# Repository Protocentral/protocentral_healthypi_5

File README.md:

<div align="center">

# HealthyPi 5

### The open-source vital signs monitor you can actually build on.

ECG · Respiration · PPG · SpO₂ · Temperature — streamed live over USB, Bluetooth LE or Wi-Fi
from a single Raspberry Pi HAT-sized board.

</div>

---

## Why HealthyPi 5

HealthyPi 5 pairs **high-precision analog front ends** — 18-bit ECG and 22-bit PPG converters from Maxim
and TI — with a design that is open all the way down.

|  |  |
| --- | --- |
| **Five biosignals, one board** | ECG, respiration, PPG, SpO₂ and temperature simultaneously. |
| **Lossless by design** | The RP2040's two cores split acquisition from everything else — 128 SPS sampling is guaranteed by the architecture, not by tuning. |
| **Connect however you like** | USB-C, BLE or Wi-Fi to OpenView — or log to the onboard microSD with no computer attached. |
| **Genuinely open** | CERN-OHL-P v2 hardware, MIT software, [OSHWA-certified IN000046](https://certification.oshwa.org/in000046.html). Commercial use permitted. |
| **Built to extend** | Qwiic/I²C connectors add GSR, EEG, EMG or any other sensor. |

<div align="center">

<p><sub><b>Live in OpenView</b> — ECG, respiration and PPG over BLE, with recording to disk</sub></p>
</div>

## What you can measure

| Signal | Front end | Notes |
| --- | --- | --- |
| **ECG** | Maxim MAX30001 | 18-bit, 128 SPS, 3-electrode cable included |
| **Respiration** | Maxim MAX30001 | Bio-impedance, from the same electrodes |
| **PPG / SpO₂** | TI AFE4400 | 22-bit, red + IR; Nellcor-compatible probe included |
| **Body temperature** | Maxim MAX30205 | Qwiic/I²C skin probe included |
| **Anything else** | Your sensor | Qwiic connectors — GSR, EEG, EMG, … |

## Hardware at a glance

- **RP2040** dual-core ARM Cortex-M0+ main MCU, 16 MB flash
- **ESP32-C3** RISC-V co-processor for Bluetooth LE and Wi-Fi
- **40-pin Raspberry Pi HAT** connector
- **2× USB Type-C** — one per MCU
- **microSD** slot for onboard recording
- **Li-Ion** battery management with USB charging
- **75.5 × 56 × 17 mm**

> Board revisions **5.2 through 5.7 are electrically identical** — one pin map serves all of them.

## Get started

**1. Get a board** — [ProtoCentral Store](https://protocentral.com/product/healthypi-5-vital-signs-monitoring-hat-kit/) · [Mouser](https://www.mouser.com/c/?m=ProtoCentral&q=HealthyPi%205) · [Crowd Supply](https://www.crowdsupply.com/protocentral/healthypi-5)

**2. Install [OpenView](https://github.com/Protocentral/protocentral_openview/releases)** — Windows, macOS, Linux, Android or iOS.

**3. Connect** over USB, BLE or Wi-Fi and start streaming. Boards ship pre-flashed.

Then see the [documentation](https://protocentral.com/product/healthypi-5-vital-signs-monitoring-hat-kit/docs/) for electrode placement, wiring and the streaming data format.

<div align="center">

<p><sub><b>In the kit</b> — board, SpO₂ probe, ECG cable, temperature probe, headers and 20 electrodes</sub></p>
</div>

## Software & documentation

This repository holds the **hardware design files**. Everything else lives in its own repository:

| | Repository | What it is |
| --- | --- | --- |
| **App** | [protocentral_openview](https://github.com/Protocentral/protocentral_openview) | **OpenView** — the main GUI. Flutter app for Windows, macOS, Linux, Android and iOS. [Downloads](https://github.com/Protocentral/protocentral_openview/releases) |
| **Firmware** (RP2040) | [protocentral_healthypi_5_firmware](https://github.com/Protocentral/protocentral_healthypi_5_firmware) | Arduino firmware and library — tutorial sketches plus the dual-core NEXT firmware. |
| **Firmware** (ESP32-C3) | [healthybridge-esp32](https://github.com/Protocentral/healthybridge-esp32) | HealthyBridge — wireless co-processor: BLE, Wi-Fi, MQTT, web dashboard. |
| **Docs** | [protocentral.com/healthypi](https://protocentral.com/healthypi/) | Setup, wiring, streaming formats, troubleshooting. |

> **Upgrading firmware?** The RP2040 and ESP32-C3 firmwares must be updated together — v2 changed the protocol between them.

## What's in this repository

| Path | Contents |
| --- | --- |
| [`hardware/`](hardware/) | Eagle `.sch`/`.brd`, BOMs and schematic PDFs — main board revs 5.3–5.7, Pro-Carrier 5.2, ST7796 display add-on 5.2, and enclosure STLs |
| [`docs/images/`](docs/images/) | Images used in this README |
| [`archived/`](archived/) | Unmaintained, kept for reference: the old Processing GUI and Python/LSL scripts, both superseded by OpenView |

## Support

Hardware and errata → [issues here](https://github.com/Protocentral/protocentral_healthypi_5/issues). Firmware → [RP2040](https://github.com/Protocentral/protocentral_healthypi_5_firmware/issues) or [ESP32-C3](https://github.com/Protocentral/healthybridge-esp32/issues). App → [OpenView](https://github.com/Protocentral/protocentral_openview/issues). PRs welcome.

> [!IMPORTANT]
> **HealthyPi 5 is not a medical device.** It is not certified for diagnosis, treatment or any clinical
> use, and must never be relied on for medical decisions — it is for education, research and development
> only. When connected to a person, power the board **only** from a battery or a properly isolated supply.

## License

| | Licence |
| --- | --- |
| **Hardware** (`hardware/`) | [CERN-OHL-P v2](https://ohwr.org/cern_ohl_p_v2.txt) — permissive; you may build and sell products based on this design |
| **Software** | [MIT](http://opensource.org/licenses/MIT) |
| **Documentation** | [CC BY-SA 4.0](http://creativecommons.org/licenses/by-sa/4.0/) |

Distributed WITHOUT ANY EXPRESS OR IMPLIED WARRANTY. Full terms in [LICENSE.md](LICENSE.md).

---

<div align="center">

**Part of the HealthyPi family** — [HealthyPi 5](https://protocentral.com/healthypi/) · [HealthyPi 6](https://www.crowdsupply.com/protocentral/healthypi-6) · [HealthyPi Move](https://protocentral.com/product/healthypi-move/)

<sub>Designed and built by <a href="https://protocentral.com">ProtoCentral Electronics</a> — open-source biomedical hardware, from sensor to signal.</sub>

</div>

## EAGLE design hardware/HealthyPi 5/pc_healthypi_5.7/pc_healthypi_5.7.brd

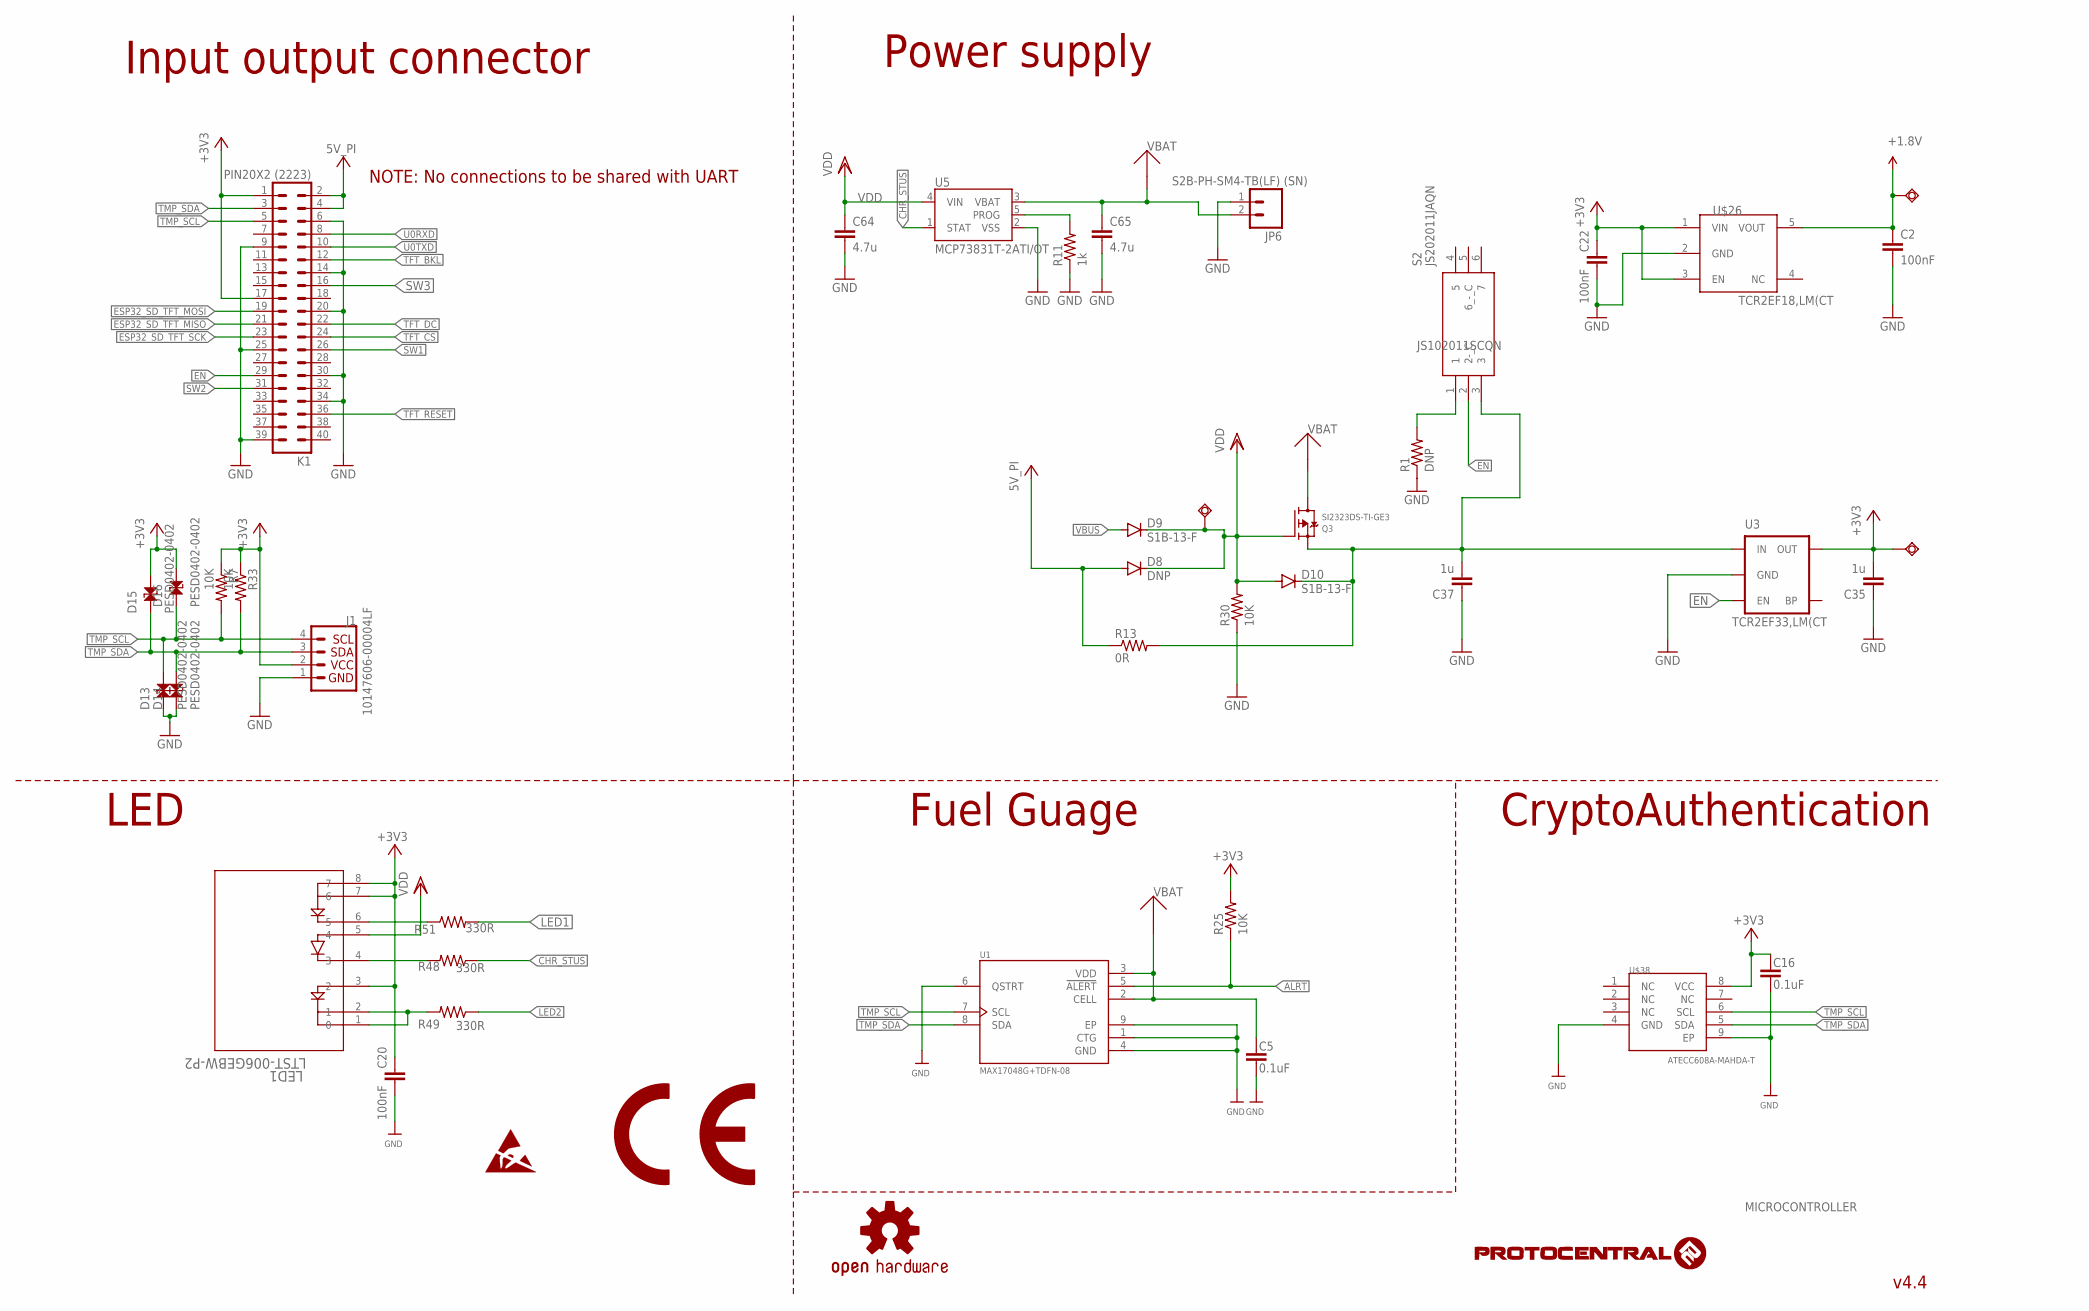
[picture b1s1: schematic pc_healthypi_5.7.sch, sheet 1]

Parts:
C2, C20, C22: 100nF; C0402
C5, C16: 0.1uF; 0402-TIGHT
C35, C37: 1u; C0402
C64, C65: 4.7u; C0805
D8: DNP; SOD-123_MINI-SMA
D9, D10: S1B-13-F; SOD-123_MINI-SMA
D13, D14, D15, D16: PESD0402-0402; 0402
J1: 10147606-00004LF; JST04_1MM_RA
JP6: S2B-PH-SM4-TB(LF) (SN); JST-2-SMD
K1: PIN20X2 (2223); PIN_20X2
LED1: LTST-006GEBW-P2; LTST-008BGEW_LTO
Q3: SI2323DS-TI-GE3; SOT23-R
R1: DNP; R0402
R7, R30, R33: 10K; R0402
R11: 1k; R0402
R13: 0R; 0805
R25: 10K; 0402-RES
R48, R49, R51: 330R; 0402-RES
S2: JS202011JAQN
SWIO1, SWIO5, SWIO7: TPSQTP11R; TP11R
U1: MAX17048G+TDFN-08; SON50P200X200X80-9N
U3: TCR2EF33,LM(CT; SOT23-5
U5: MCP73831T-2ATI/OT; SOT23-5
U$5: OSHW-LOGOM; OSHW-LOGO-M
U$26: TCR2EF18,LM(CT; SOT95P285X140-5N
U$38: ATECC608A-MAHDA-T; PSON50P200X300X60-9N

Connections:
+1.8V: C2.1, SWIO5.TP, U$26.5 (VOUT); also elsewhere on the board
+3V3: C16.1, C20.1, C22.1, C35.2, D15.2, D16.2, J1.2, K1.1, K1.17, LED1.3 (2), LED1.7 (6), LED1.8 (7), R7.1, R25.2, R33.1, SWIO1.TP, U3.5 (OUT), U$26.1 (VIN), U$26.3 (EN), U$38.8 (VCC); also elsewhere on the board
+5V: D8.A, K1.2, K1.4, R13.1
ALRT: R25.1, U1.5 (!ALERT)
CHR_STUS: R48.1, U5.1 (STAT)
EN: K1.29, S2.2 (2-_C), U3.3 (EN)
ESP32_SD_TFT_MISO: K1.21; also elsewhere on the board
ESP32_SD_TFT_MOSI: K1.19; also elsewhere on the board
ESP32_SD_TFT_SCK: K1.23; also elsewhere on the board
GND: C2.2, C5.2, C16.2, C20.2, C22.2, C35.1, C37.1, C64.2, C65.2, D13.1, D14.1, J1.1, JP6.1, K1.6, K1.9, K1.14, K1.20, K1.25, K1.30, K1.34, K1.39, R1.1, R11.1, R30.1, U1.1 (CTG), U1.4 (GND), U1.6 (QSTRT), U1.9 (EP), U3.2 (GND), U5.2 (VSS), U$26.2 (GND), U$38.4 (GND), U$38.9 (EP); also elsewhere on the board
LED1: R51.2; also elsewhere on the board
LED2: R49.1; also elsewhere on the board
unnamed: R1.2, S2.1
unnamed: LED1.4 (3), R48.2
unnamed: C37.2, D10.C, Q3.2 (S), R13.2, S2.3, U3.1 (IN)
unnamed: R11.2, U5.5 (PROG)
unnamed: LED1.1 (0), LED1.2 (1), R49.2
unnamed: LED1.6 (5), R51.1
SW1: K1.26; also elsewhere on the board
SW2: K1.31; also elsewhere on the board
SW3: K1.16; also elsewhere on the board
TFT_BKL: K1.12; also elsewhere on the board
TFT_CS: K1.24; also elsewhere on the board
TFT_DC: K1.22; also elsewhere on the board
TFT_RESET: K1.36; also elsewhere on the board
TMP_SCL: D13.2, D16.1, J1.4, K1.5, R7.2, U1.7 (SCL), U$38.6 (SCL); also elsewhere on the board
TMP_SDA: D14.2, D15.1, J1.3, K1.3, R33.2, U1.8 (SDA), U$38.5 (SDA); also elsewhere on the board
U0RXD: K1.8; also elsewhere on the board
U0TXD: K1.10; also elsewhere on the board
VBAT: C5.1, C65.1, JP6.2, Q3.3 (D), U1.2 (CELL), U1.3 (VDD), U5.3 (VBAT)
VBUS: D9.A; also elsewhere on the board
VDD: C64.1, D8.C, D9.C, D10.A, LED1.5 (4), Q3.1 (G), R30.2, SWIO7.TP, U5.4 (VIN)

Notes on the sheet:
v4.4
MICROCONTROLLER
JS102011SCQN
NOTE: No connections to be shared with UART
LED
Input output connector
Power supply
Fuel Guage
CryptoAuthentication

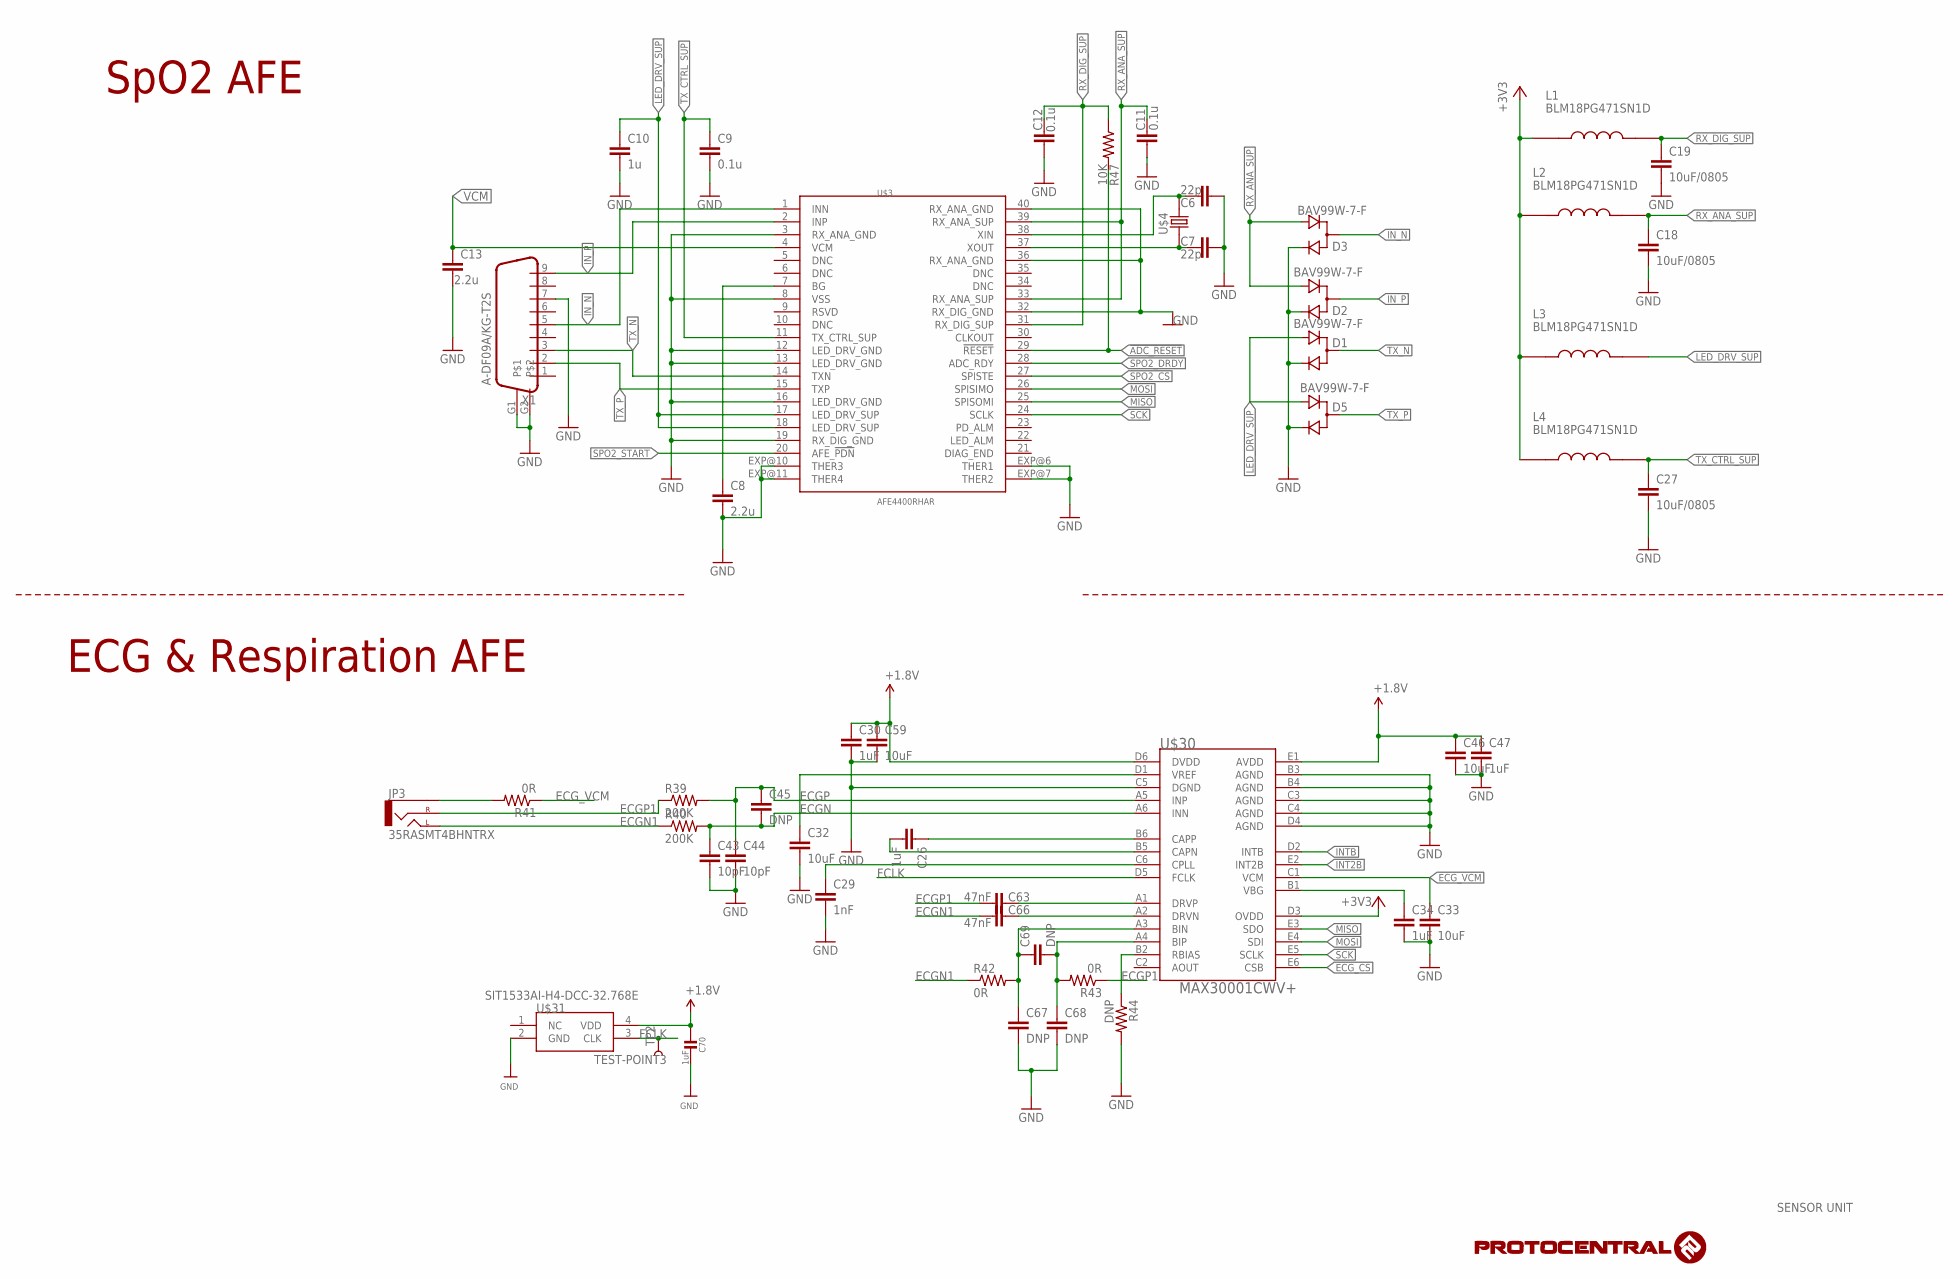
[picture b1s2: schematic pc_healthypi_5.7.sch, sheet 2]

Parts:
C6, C7: 22p; C0402
C8, C13: 2.2u; C0402
C9, C11, C12: 0.1u; C0402
C10: 1u; C0805
C18, C19, C27: 10uF/0805; C0805
C26: 1uF; C0805
C29: 1nF; C0402
C30, C34, C47: 1uF; C0402
C32, C33, C46, C59: 10uF; C0805
C43, C44: 10pF; C0402
C45, C67, C68, C69: DNP; C0402
C63, C66: 47nF; C0402
C70: 1uF; 0402
D1, D2, D3, D5: BAV99W-7-F; SOT323
JP3: 35RASMT4BHNTRX; AUDIO-JACK-3.5MM-SMD
L1, L2, L3, L4: BLM18PG471SN1D; INDC2012X105N
R39, R40: 200K; 0805
R41: 0R; 0805
R42, R43: 0R; 0402-RES
R44: DNP; 0402-RES
R47: 10K; R0402
TP2: TEST-POINT3; PAD.03X.03
U$3: AFE4400RHAR; QFN-40
U$4: ABM3
U$30: MAX30001CWV+; 30WLP
U$31: SIT1533AI-H4-DCC-32.768E; SIT1533
X1: A-DF09A/KG-T2S; DB9

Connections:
!ADC_RESET: R47.2, U$3.29 (!RESET)
+1.8V: C30.1, C46.1, C47.1, C59.1, C70.1, U$30.D6 (DVDD), U$30.E1 (AVDD), U$31.4 (VDD); also elsewhere on the board
+3V3: L1.1, L2.1, L3.1, L4.1, U$30.D3 (OVDD); also elsewhere on the board
ECGN: C43.1, C45.2, R40.2, U$30.A6 (INN)
ECGN1: C66.1, JP3.TIP (LEFT), R40.1, R42.1
ECGP: C44.1, C45.1, R39.2, U$30.A5 (INP)
ECGP1: C63.1, JP3.RING (RIGHT), R39.1, R43.1
ECG_CS: U$30.E6 (CSB); also elsewhere on the board
ECG_VCM: C33.1, R41.1, U$30.C1 (VCM)
FCLK: TP2.P$1, U$30.D5 (FCLK), U$31.3 (CLK)
GND: C6.1, C7.1, C8.2, C9.2, C10.2, C11.2, C12.2, C13.2, C18.2, C19.2, C27.2, C29.2, C30.2, C32.2, C33.2, C34.2, C43.2, C44.2, C46.2, C47.2, C59.2, C67.2, C68.2, C70.2, D1.2 (C), D2.2 (C), D3.2 (C), D5.2 (C), R44.2, U$3.3 (RX_ANA_GND), U$3.8 (VSS), U$3.12 (LED_DRV_GND), U$3.13 (LED_DRV_GND), U$3.16 (LED_DRV_GND), U$3.19 (RX_DIG_GND), U$3.32 (RX_DIG_GND), U$3.36 (RX_ANA_GND), U$3.40 (RX_ANA_GND), U$3.EXP@6 (THER1), U$3.EXP@7 (THER2), U$3.EXP@10 (THER3), U$3.EXP@11 (THER4), U$30.B3 (AGND), U$30.B4 (AGND), U$30.C3 (AGND), U$30.C4 (AGND), U$30.C5 (DGND), U$30.D4 (AGND), U$31.2 (GND), X1.7, X1.G1, X1.G2; also elsewhere on the board
INT2B: U$30.E2 (INT2B)
INTB: U$30.D2 (INTB); also elsewhere on the board
IN_N: D3.1 (CA), U$3.1 (INN), X1.5
IN_P: D2.1 (CA), U$3.2 (INP), X1.9
LED_DRV_SUP: C10.1, D1.3 (A), D5.3 (A), L3.2, U$3.17 (LED_DRV_SUP), U$3.18 (LED_DRV_SUP)
MISO: U$3.25 (SPISOMI), U$30.E3 (SDO); also elsewhere on the board
MOSI: U$3.26 (SPISIMO), U$30.E4 (SDI); also elsewhere on the board
unnamed: C6.2, U$3.38 (XIN), U$4.2
unnamed: C7.2, U$3.37 (XOUT), U$4.1
unnamed: C8.1, U$3.7 (BG)
unnamed: C29.1, U$30.C6 (CPLL)
unnamed: C26.2, U$30.B5 (CAPN)
unnamed: C32.1, U$30.D1 (VREF)
unnamed: C34.1, U$30.B1 (VBG)
unnamed: JP3.SLEEVE, R41.2
unnamed: C26.1, U$30.B6 (CAPP)
unnamed: C63.2, U$30.A1 (DRVP)
unnamed: C66.2, U$30.A2 (DRVN)
unnamed: C67.1, C69.1, R42.2, U$30.A3 (BIN)
unnamed: C68.1, C69.2, R43.2, U$30.A4 (BIP)
unnamed: R44.1, U$30.B2 (RBIAS)
RX_ANA_SUP: C11.1, C18.1, D2.3 (A), D3.3 (A), L2.2, U$3.33 (RX_ANA_SUP), U$3.39 (RX_ANA_SUP)
RX_DIG_SUP: C12.1, C19.1, L1.2, R47.1, U$3.31 (RX_DIG_SUP)
SCK: U$3.24 (SCLK), U$30.E5 (SCLK); also elsewhere on the board
SPO2_CS: U$3.27 (SPISTE); also elsewhere on the board
SPO2_DRDY: U$3.28 (ADC_RDY); also elsewhere on the board
SPO2_START: U$3.20 (AFE_!PDN); also elsewhere on the board
TX_CTRL_SUP: C9.1, C27.1, L4.2, U$3.11 (TX_CTRL_SUP)
TX_N: D1.1 (CA), U$3.14 (TXN), X1.3
TX_P: D5.1 (CA), U$3.15 (TXP), X1.2
VCM: C13.1, U$3.4 (VCM)

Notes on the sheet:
SENSOR UNIT
SpO2 AFE
ECG & Respiration AFE

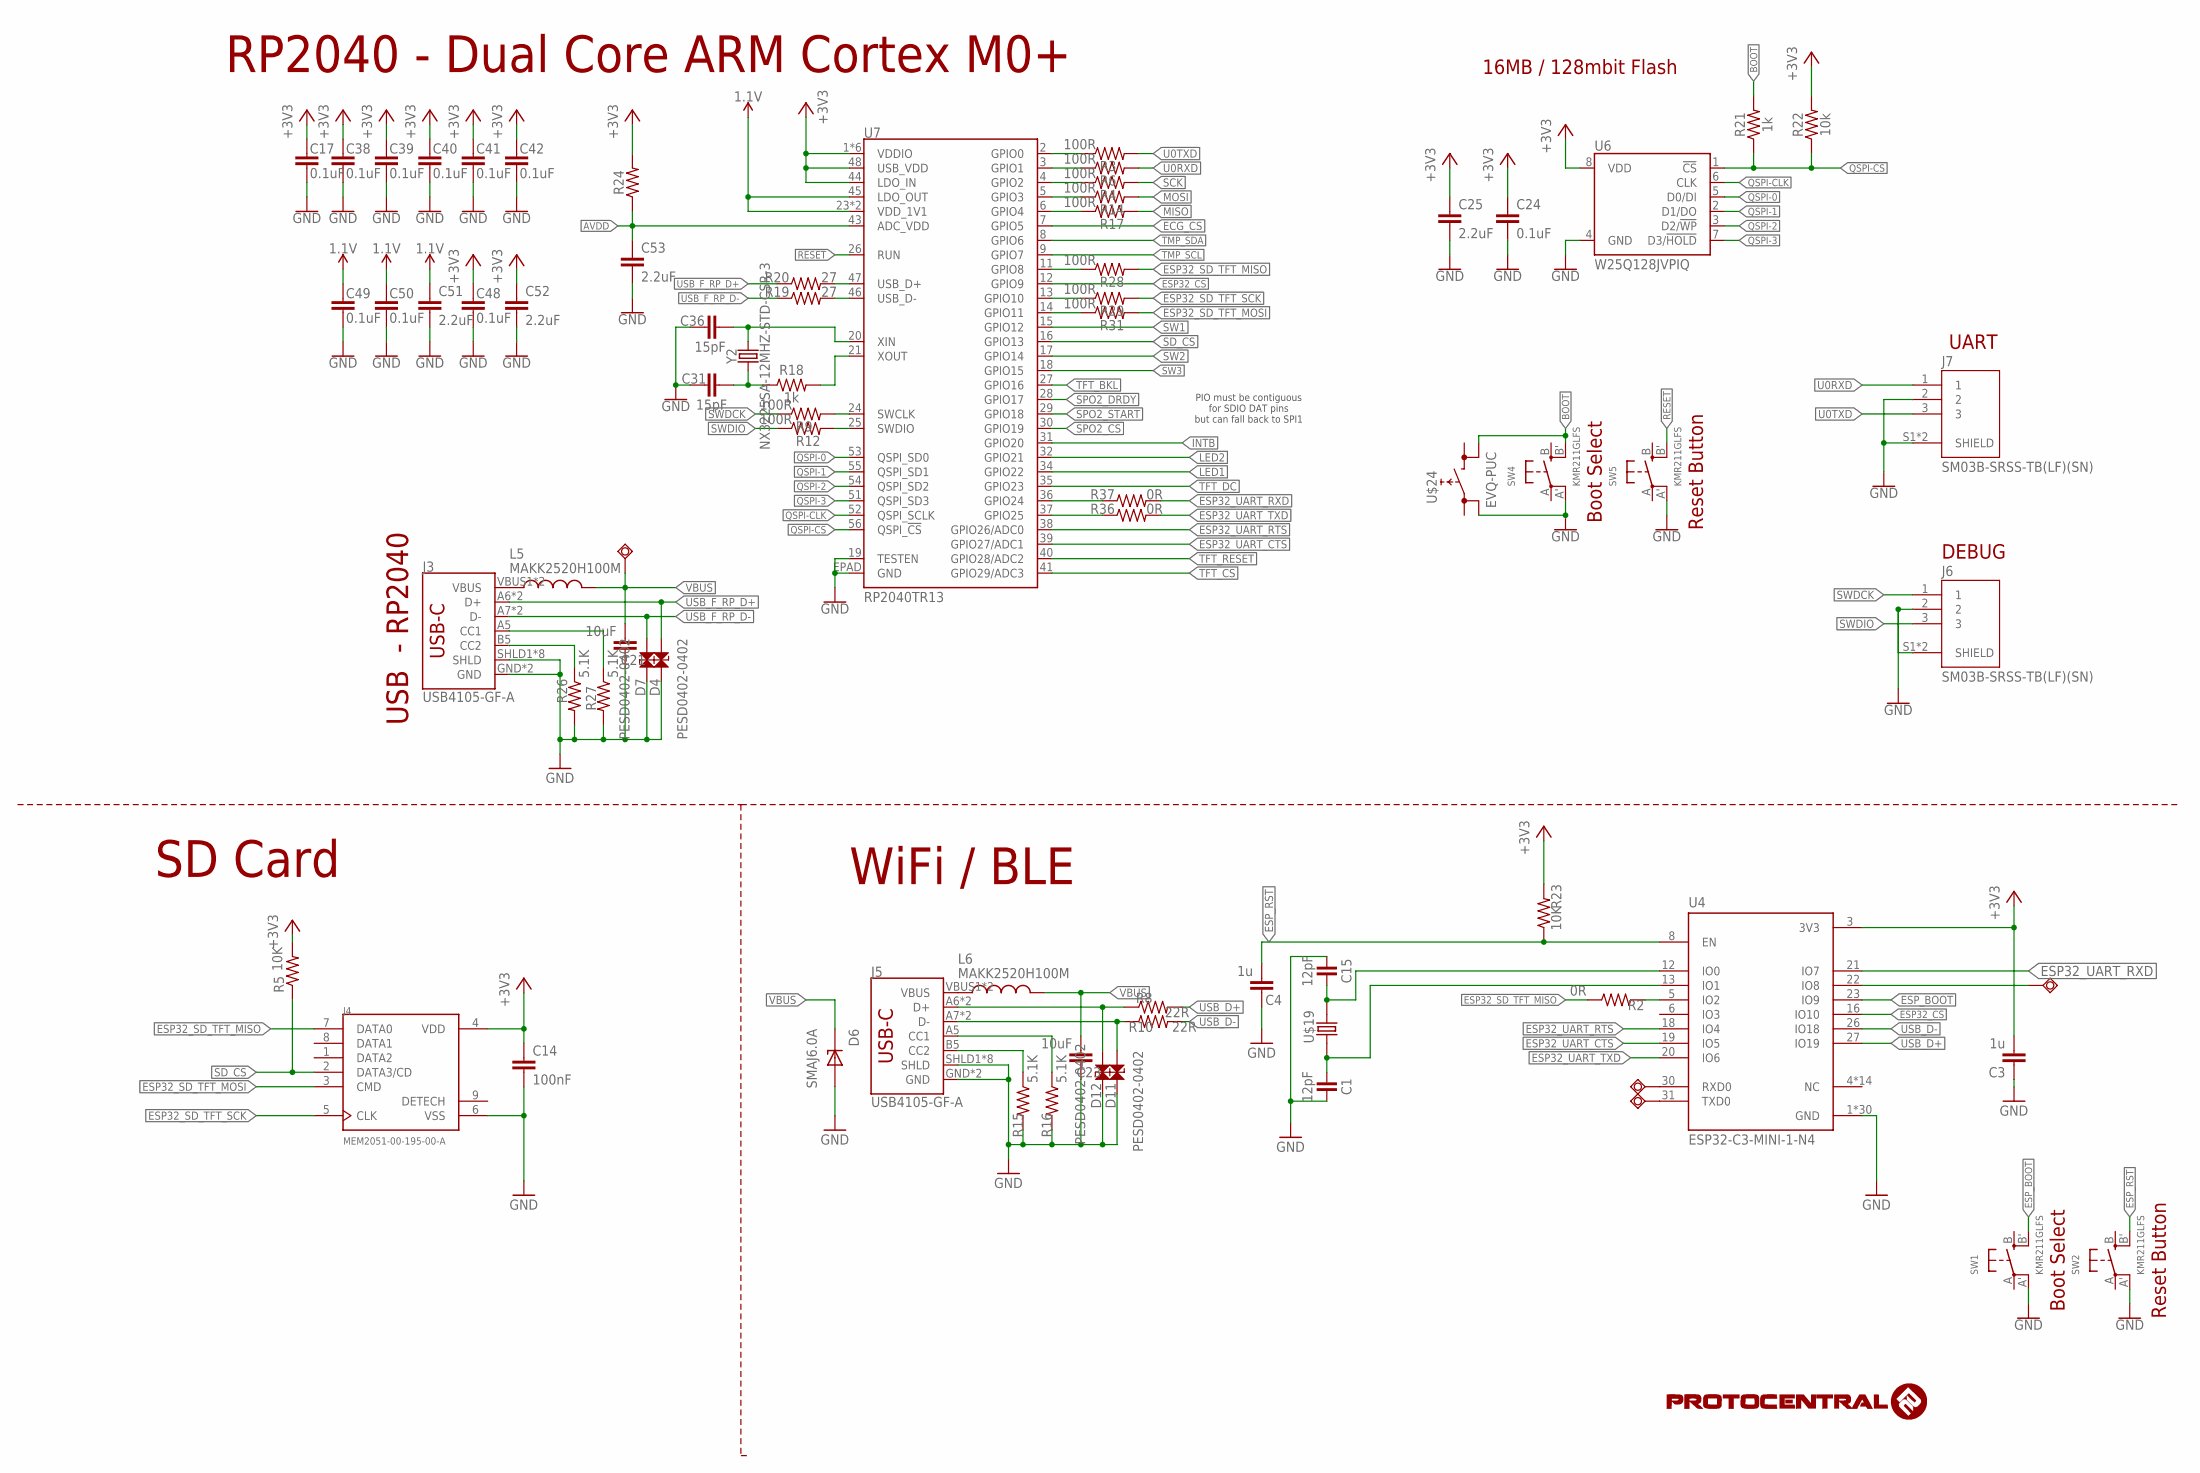
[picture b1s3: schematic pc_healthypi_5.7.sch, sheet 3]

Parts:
C1, C15: 12pF; C0402
C3, C4: 1u; C0402
C14: 100nF; C0402
C17, C24, C38, C39, C40, C41, C42, C48, C49, C50: 0.1uF; 0402-TIGHT
C21, C23: 10uF; C0805
C25, C51, C52, C53: 2.2uF; 0402-TIGHT
C31, C36: 15pF; 0402-TIGHT
D4, D7, D11, D12: PESD0402-0402; 0402
D6: SMAJ6.0A; DIOM4325X250N
J3, J5: USB4105-GF-A; USB-C-16P
J4: MEM2051-00-195-00-A; GCT_MEM2051-00-195-00-A
J6, J7: SM03B-SRSS-TB(LF)(SN); JST_SM03B-SRSS-TB(LF)(SN)
L5, L6: MAKK2520H100M; INDC2520X100N
R2: 0R; R0402
R3, R4, R6, R9, R12, R14, R17, R28, R29, R31: 100R; R0402
R5, R23: 10K; R0402
R8, R10: 22R; R0402
R15, R16, R26, R27: 5.1K; R0402
R18, R21: 1k; 0402-TIGHT
R19, R20: 27; 0402-TIGHT
R22: 10k; 0402-TIGHT
R24: 200OHM-0402T-1/16W-1%; 0402-TIGHT
R36, R37: 0R; 0402-TIGHT
SW1, SW2, SW4, SW5: KMR211GLFS; BTN_KMR2_4.6X2.8
SWIO2, SWIO8, SWIO9: TPSQTP11R; TP11R
TP5: TPSQTP11R; TP11R
U4: ESP32-C3-MINI-1-N4; XCVR_ESP32-C3-MINI-1-N4
U6: W25Q128JVPIQ; WSON-8-6X5-SKINNY_CENTERPAD
U7: RP2040TR13; QFN-56
U$19: 520-327-12.5-34B(32.768KHZ); ECX-31B
U$24: EVQ-PUC
Y2: NX3225SA-12MHZ-STD-CSR-3; CRYSTAL-SMD-2X2.5MM

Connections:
1.1V: C49.1, C50.1, C51.1, U7.23 (VDD_1V1), U7.45 (LDO_OUT), U7.50 (VDD_1V1)
!RESET!: SW5.B' (S1), U7.26 (RUN)
+3V3: C3.2, C14.1, C17.1, C24.1, C25.1, C38.1, C39.1, C40.1, C41.1, C42.1, C48.1, C52.1, J4.4 (VDD), R5.2, R22.2, R23.2, R24.2, U4.3 (3V3), U6.8 (VDD), U7.1 (VDDIO), U7.10 (VDDIO), U7.22 (VDDIO), U7.33 (VDDIO), U7.42 (VDDIO), U7.44 (LDO_IN), U7.48 (USB_VDD), U7.49 (VDDIO); also elsewhere on the board
AVDD: C53.1, R24.1, U7.43 (ADC_VDD)
BOOT: R21.2, SW4.B' (S1), U$24.2 (1)
D+: D12.2, J5.A6 (D+), J5.B6 (D+), R8.1
D-: D11.2, J5.A7 (D-), J5.B7 (D-), R10.1
ECG_CS: U7.7 (GPIO5); also elsewhere on the board
ESP32_CS: U4.16 (IO10), U7.12 (GPIO9)
ESP32_MISO: R2.2, U4.5 (IO2)
ESP32_SD_TFT_MISO: J4.7 (DATA0), R2.1, R28.2; also elsewhere on the board
ESP32_SD_TFT_MOSI: J4.3 (CMD), R31.2; also elsewhere on the board
ESP32_SD_TFT_SCK: J4.5 (CLK), R29.2; also elsewhere on the board
ESP32_UART_CTS: U4.19 (IO5), U7.39 (GPIO27/ADC1)
ESP32_UART_RTS: U4.18 (IO4), U7.38 (GPIO26/ADC0)
ESP32_UART_RXD: R37.2, U4.21 (IO7)
ESP32_UART_TXD: R36.2, U4.20 (IO6)
ESP_BOOT: SW1.B' (S1), U4.23 (IO9)
ESP_RST: C4.2, R23.1, SW2.B' (S1), U4.8 (EN)
GND: C1.2, C3.1, C4.1, C14.2, C15.1, C17.2, C21.1, C23.1, C24.2, C25.2, C31.1, C36.1, C38.2, C39.2, C40.2, C41.2, C42.2, C48.2, C49.2, C50.2, C51.2, C52.2, C53.2, D4.1, D6.A, D7.1, D11.1, D12.1, J3.GND, J3.GND2 (GND), J3.SHLD1 (SHLD), J3.SHLD2 (SHLD), J3.SHLD3 (SHLD), J3.SHLD4 (SHLD), J3.SHLD5 (SHLD), J3.SHLD6 (SHLD), J3.SHLD7 (SHLD), J3.SHLD8 (SHLD), J4.6 (VSS), J5.GND, J5.GND2 (GND), J5.SHLD1 (SHLD), J5.SHLD2 (SHLD), J5.SHLD3 (SHLD), J5.SHLD4 (SHLD), J5.SHLD5 (SHLD), J5.SHLD6 (SHLD), J5.SHLD7 (SHLD), J5.SHLD8 (SHLD), J6.2, J6.S1 (SHIELD), J6.S2 (SHIELD), J7.2, J7.S1 (SHIELD), J7.S2 (SHIELD), R15.2, R16.2, R26.2, R27.2, SW1.A' (P1), SW2.A' (P1), SW4.A' (P1), SW5.A' (P1), U4.1 (GND), U4.2 (GND), U4.11 (GND), U4.14 (GND), U4.36 (GND), U4.37 (GND), U4.38 (GND), U4.39 (GND), U4.40 (GND), U4.41 (GND), U4.42 (GND), U4.43 (GND), U4.44 (GND), U4.45 (GND), U4.46 (GND), U4.47 (GND), U4.48 (GND), U4.49_1 (GND), U4.49_2 (GND), U4.49_3 (GND), U4.49_4 (GND), U4.49_5 (GND), U4.49_6 (GND), U4.49_7 (GND), U4.49_8 (GND), U4.49_9 (GND), U4.50 (GND), U4.51 (GND), U4.52 (GND), U4.53 (GND), U6.4 (GND), U7.19 (TESTEN), U7.EPAD (GND), U$24.3 (0); also elsewhere on the board
INTB: U7.31 (GPIO20); also elsewhere on the board
LED1: U7.34 (GPIO22); also elsewhere on the board
LED2: U7.32 (GPIO21); also elsewhere on the board
MISO: R17.2; also elsewhere on the board
MOSI: R14.2; also elsewhere on the board
unnamed: R4.1, U7.4 (GPIO2)
unnamed: R3.1, U7.2 (GPIO0)
unnamed: R6.1, U7.3 (GPIO1)
unnamed: R9.2, U7.24 (SWCLK)
unnamed: J5.B5 (CC2), R15.1
unnamed: J5.A5 (CC1), R16.1
unnamed: R14.1, U7.5 (GPIO3)
unnamed: SWIO8.TP, U4.30 (RXD0)
unnamed: R18.2, U7.21 (XOUT)
unnamed: R17.1, U7.6 (GPIO4)
unnamed: SWIO9.TP, U4.31 (TXD0)
unnamed: C36.2, U7.20 (XIN), Y2.P3 (2)
unnamed: C31.2, R18.1, Y2.P1 (1)
unnamed: J3.B5 (CC2), R26.1
unnamed: R28.1, U7.11 (GPIO8)
unnamed: C15.2, U4.12 (IO0), U$19.P$2 (2)
unnamed: J3.A5 (CC1), R27.1
unnamed: C1.1, U4.13 (IO1), U$19.P$1 (1)
unnamed: R37.1, U7.36 (GPIO24)
unnamed: R36.1, U7.37 (GPIO25)
unnamed: R29.1, U7.13 (GPIO10)
unnamed: SWIO2.TP, U4.22 (IO8)
unnamed: R12.2, U7.25 (SWDIO)
unnamed: R31.1, U7.14 (GPIO11)
unnamed: J3.VBUS1 (VBUS), J3.VBUS2 (VBUS), L5.1
unnamed: J5.VBUS1 (VBUS), J5.VBUS2 (VBUS), L6.1
QSPI-0: U6.5 (D0/DI), U7.53 (QSPI_SD0)
QSPI-1: U6.2 (D1/DO), U7.55 (QSPI_SD1)
QSPI-2: U6.3 (D2/!WP!), U7.54 (QSPI_SD2)
QSPI-3: U6.7 (D3/!HOLD!), U7.51 (QSPI_SD3)
QSPI-CLK: U6.6 (CLK), U7.52 (QSPI_SCLK)
QSPI-CS: R21.1, R22.1, U6.1 (!CS!), U7.56 (QSPI_!CS!)
SCK: R4.2; also elsewhere on the board
SD_CS: J4.2 (DATA3/CD), R5.1, U7.16 (GPIO13)
SPO2_CS: U7.30 (GPIO19); also elsewhere on the board
SPO2_DRDY: U7.28 (GPIO17); also elsewhere on the board
SPO2_START: U7.29 (GPIO18); also elsewhere on the board
SW1: U7.15 (GPIO12); also elsewhere on the board
SW2: U7.17 (GPIO14); also elsewhere on the board
SW3: U7.18 (GPIO15); also elsewhere on the board
SWDCK: J6.1, R9.1
SWDIO: J6.3, R12.1
TFT_BKL: U7.27 (GPIO16); also elsewhere on the board
TFT_CS: U7.41 (GPIO29/ADC3); also elsewhere on the board
TFT_DC: U7.35 (GPIO23); also elsewhere on the board
TFT_RESET: U7.40 (GPIO28/ADC2); also elsewhere on the board
TMP_SCL: U7.9 (GPIO7); also elsewhere on the board
TMP_SDA: U7.8 (GPIO6); also elsewhere on the board
U0RXD: J7.1, R6.2; also elsewhere on the board
U0TXD: J7.3, R3.2; also elsewhere on the board
USB_D+: R8.2, U4.27 (IO19)
USB_D-: R10.2, U4.26 (IO18)
USB_F_N: R19.2, U7.46 (USB_D-)
USB_F_P: R20.2, U7.47 (USB_D+)
USB_F_RP_D+: D4.2, J3.A6 (D+), J3.B6 (D+), R20.1
USB_F_RP_D-: D7.2, J3.A7 (D-), J3.B7 (D-), R19.1
VBUS: C21.2, C23.2, D6.C, L5.2, L6.2, TP5.TP; also elsewhere on the board

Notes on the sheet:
Reset Button
RP2040 - Dual Core ARM Cortex M0+
PIO must be contiguous for SDIO DAT pins but can fall back to SPI1
Boot Select
16MB / 128mbit Flash
USB - RP2040
SD Card
WiFi / BLE
DEBUG
UART

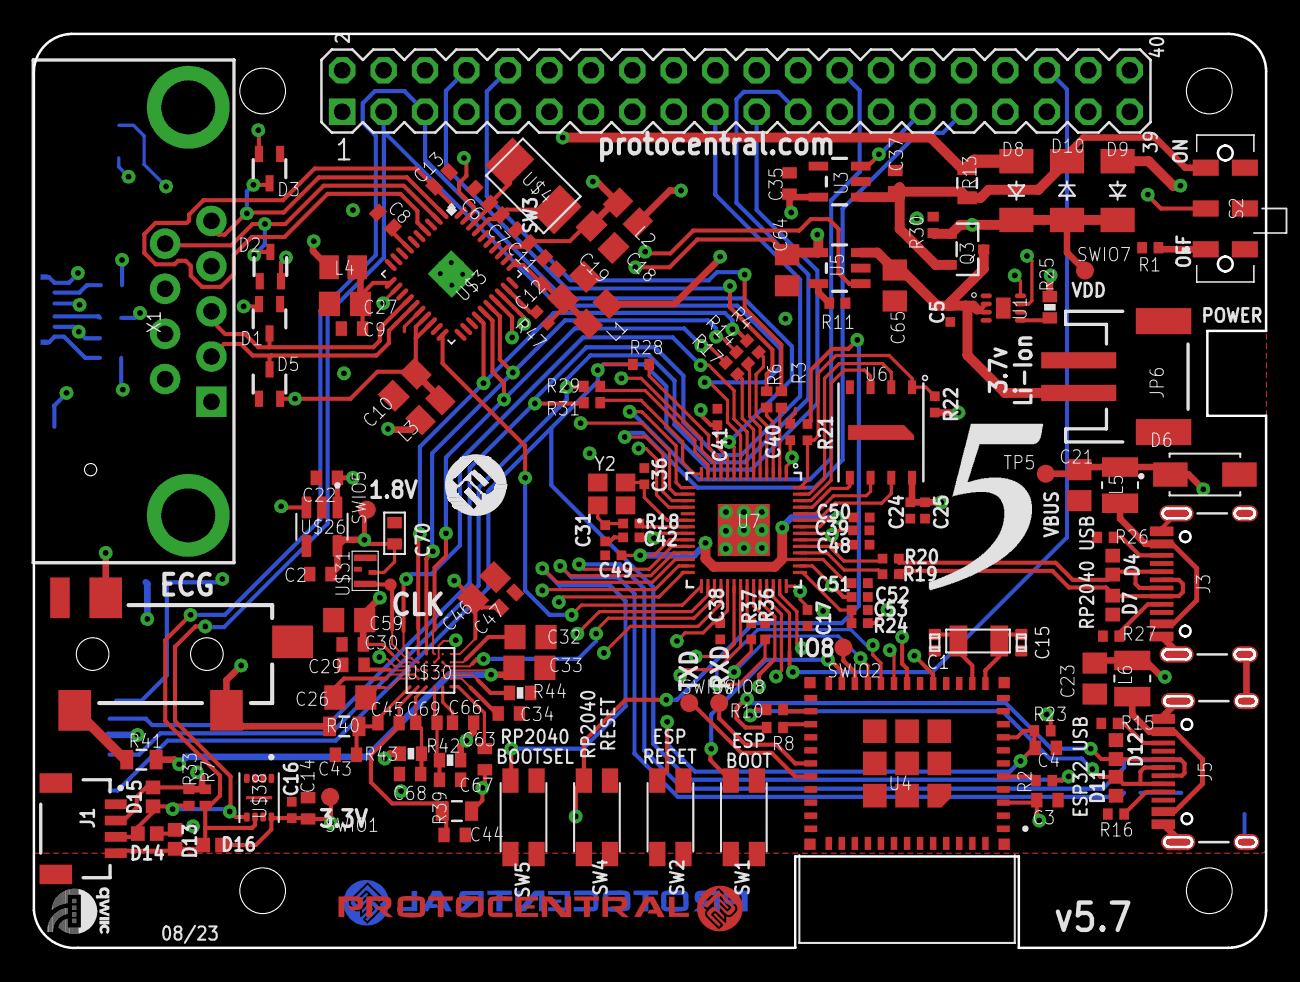
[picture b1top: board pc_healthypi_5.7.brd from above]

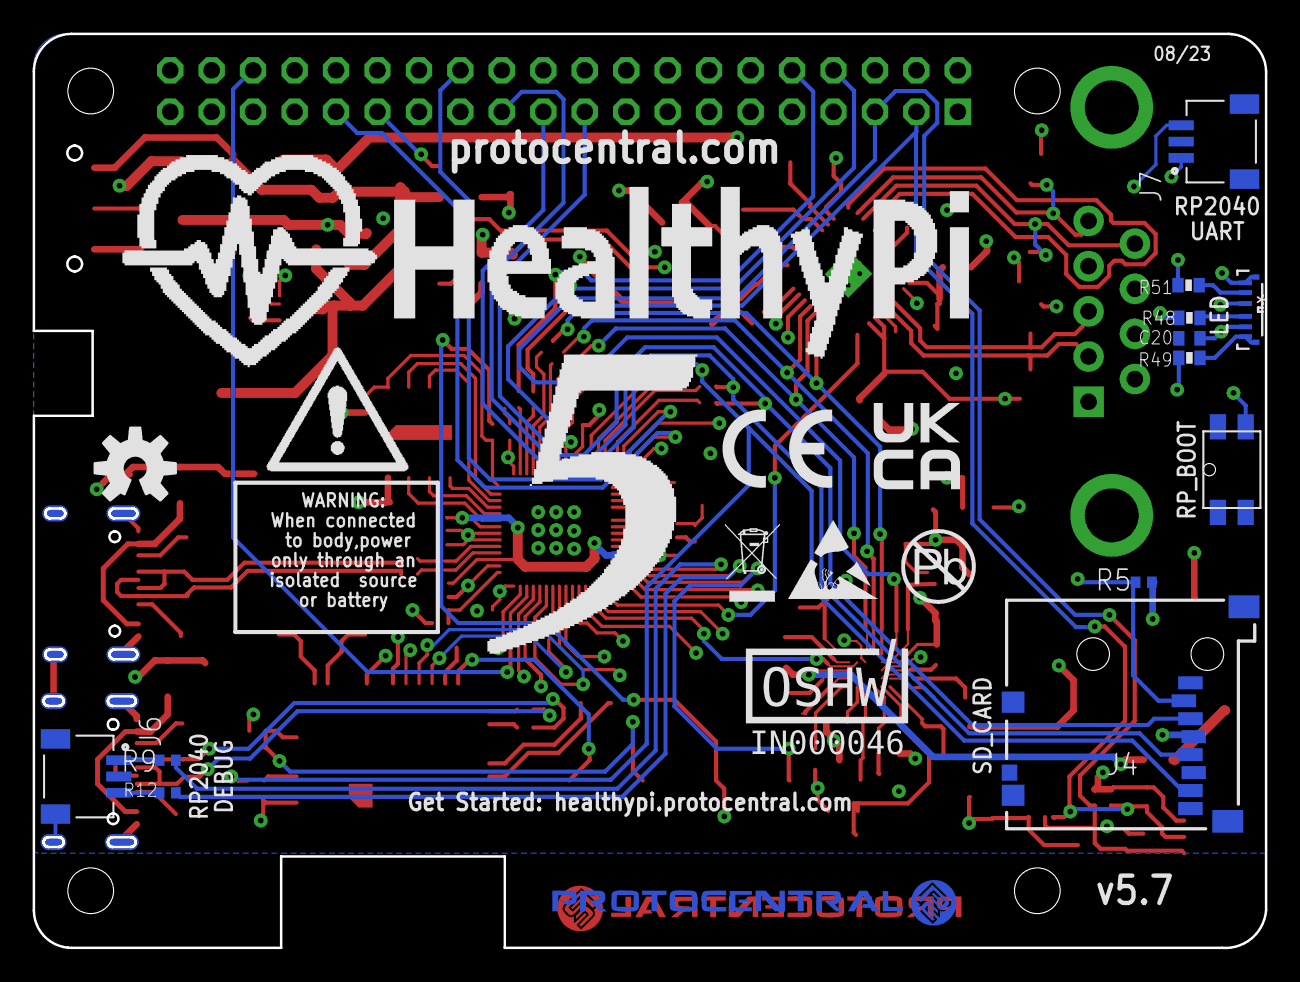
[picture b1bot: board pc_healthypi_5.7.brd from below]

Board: 4 copper layers, 75.5 x 56.0 mm, 181 parts (22 on the bottom side), 125 nets.

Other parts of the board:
U$2: HEALTHYPI_5_ONLY
U$7: OSHW_LOGO
U$14: CESYMBOLE-5MM
U$17: WARNINGSYM
U$20: HEALTHYPIV5LOGO
U$22, U$27: PC_LOGO_ONELINE_ROUND
U$35: PCROUNDLOGO
U$47: ESDSYMBOLE
U$51: UKCE
U$52: WEE_SYMBOLE
U$53: PB_FREE_SYMBOLE
U$59: QWIIC#LABEL#FULL#M#PNG

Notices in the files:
README.md:
Hardware licence: CERN-OHL-P v2
Software licence: MIT
parts and their libraries:
SparkFun-PowerSymbols: Licensing: Creative Commons ShareAlike 4.0 International - https://creativecommons.org/licenses/by-sa/4.0
COPYRIGHT: Copyright (C) 2023 Ultra Librarian. All rights reserved.
